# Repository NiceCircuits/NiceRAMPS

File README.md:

ramps_plus
==========
Forked from Ramps 1.4.

Improved version of RAMPS board with ribbon cable connecors and more.

Change log from Ramps 1.4:

- a few ribbon header connectors instead of many pinheaders

- schematic in KiCad

- compatibility with Arduino Due

- separate power supplies for heaters, bed and motors

- 0,5A OC outputs for driwing LED/fans

- SMT power transistors

- blade fuses

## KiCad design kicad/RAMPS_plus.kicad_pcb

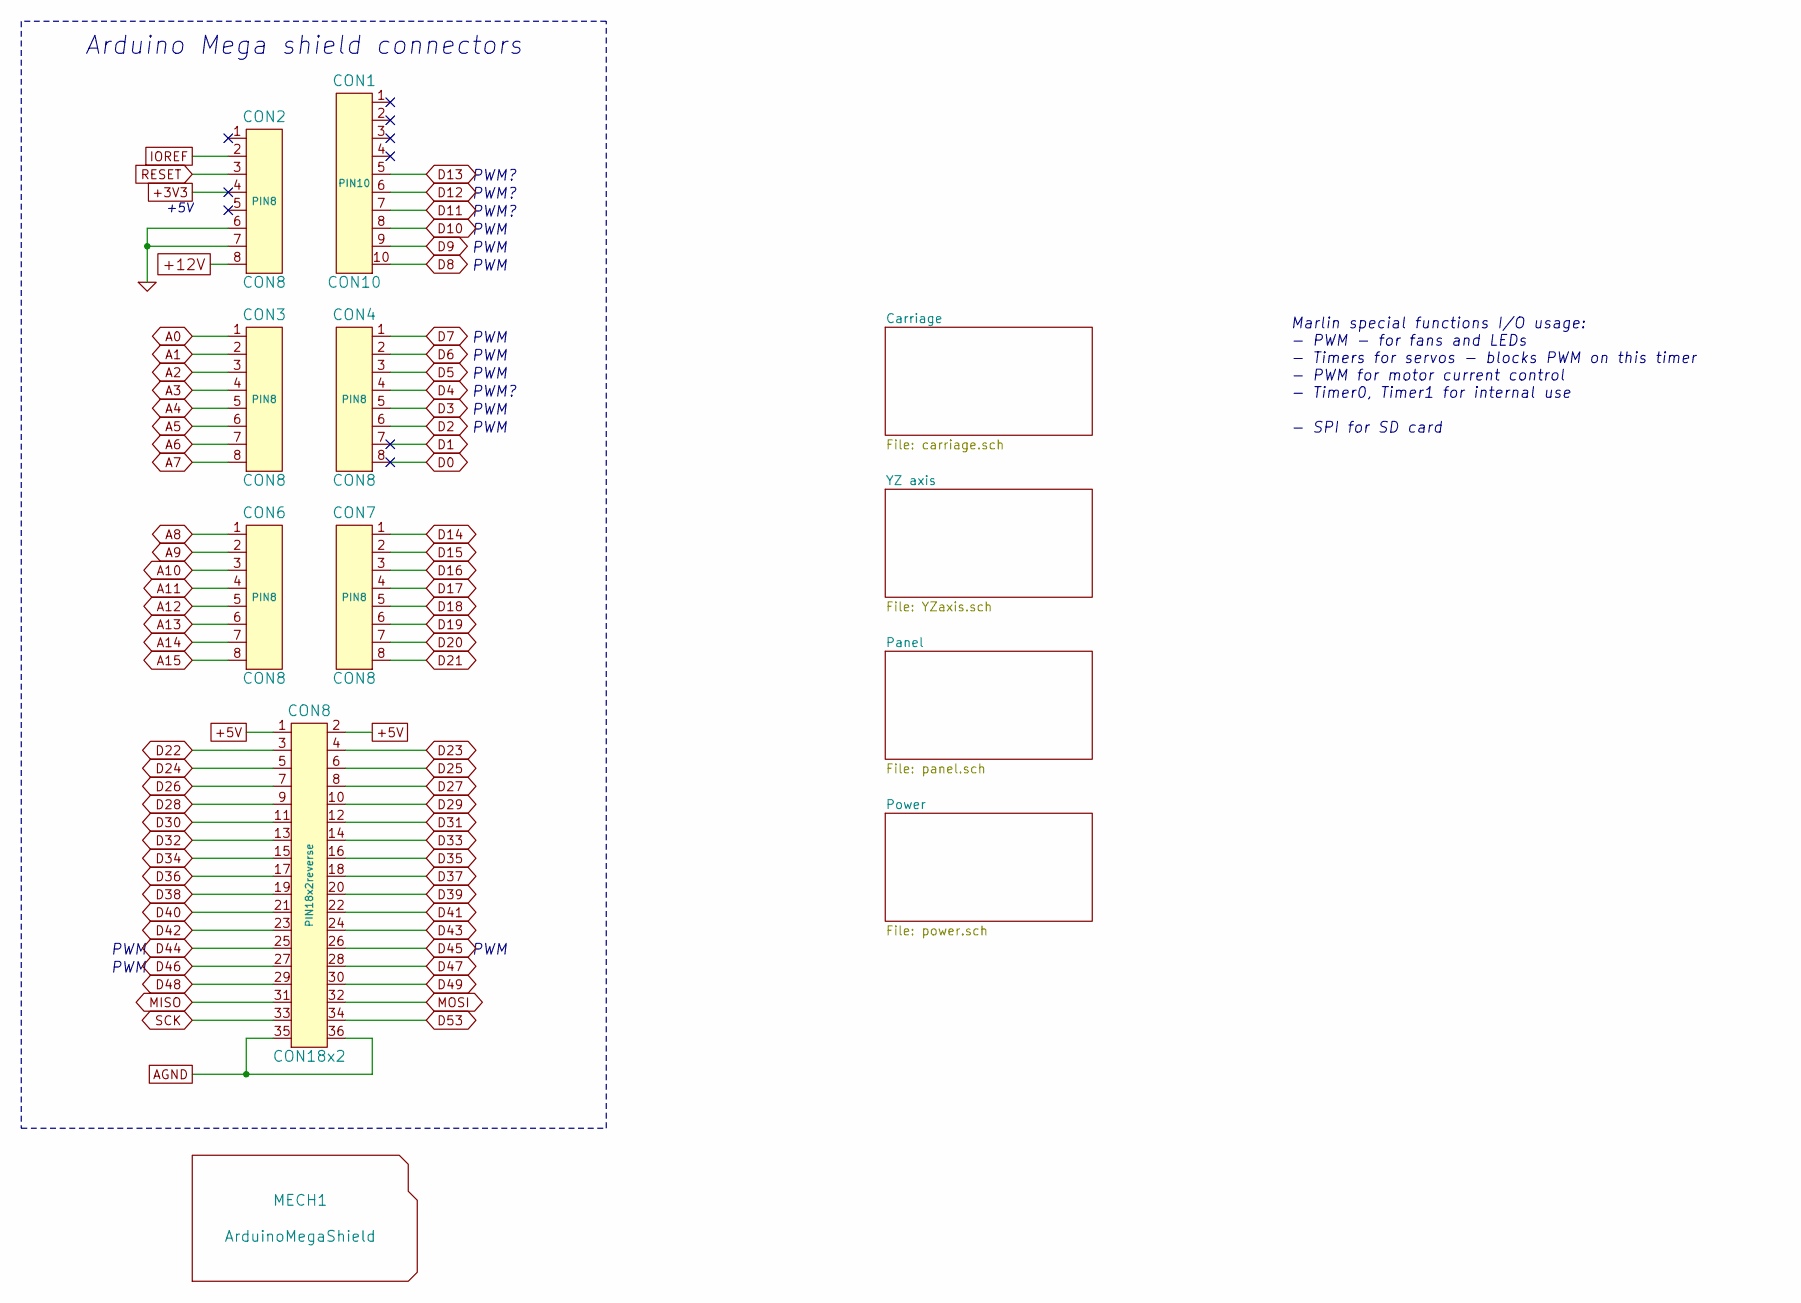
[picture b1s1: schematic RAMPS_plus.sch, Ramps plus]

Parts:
CON1: CON10; PIN10
CON2, CON3, CON4, CON6, CON7: CON8; PIN8
CON8: CON18x2; PIN18x2reverse
MECH1: ArduinoMegaShield

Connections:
+5V: CON8.1, CON8.2; also elsewhere on the board
+12V: CON2.8; also elsewhere on the board
A0: CON3.1; also elsewhere on the board
A1: CON3.2; also elsewhere on the board
A2: CON3.3; also elsewhere on the board
A4: CON3.5; also elsewhere on the board
A5: CON3.6; also elsewhere on the board
A6: CON3.7; also elsewhere on the board
A7: CON3.8; also elsewhere on the board
A8: CON6.1; also elsewhere on the board
A9: CON6.2; also elsewhere on the board
A10: CON6.3; also elsewhere on the board
A11: CON6.4; also elsewhere on the board
A12: CON6.5; also elsewhere on the board
A13: CON6.6; also elsewhere on the board
A14: CON6.7; also elsewhere on the board
A15: CON6.8; also elsewhere on the board
AGND: CON8.35, CON8.36; also elsewhere on the board
D2: CON4.6; also elsewhere on the board
D3: CON4.5; also elsewhere on the board
D4: CON4.4; also elsewhere on the board
D5: CON4.3; also elsewhere on the board
D6: CON4.2; also elsewhere on the board
D7: CON4.1; also elsewhere on the board
D8: CON1.10; also elsewhere on the board
D9: CON1.9; also elsewhere on the board
D10: CON1.8; also elsewhere on the board
D11: CON1.7; also elsewhere on the board
D12: CON1.6; also elsewhere on the board
D13: CON1.5; also elsewhere on the board
D14: CON7.1; also elsewhere on the board
D15: CON7.2; also elsewhere on the board
D16: CON7.3; also elsewhere on the board
D17: CON7.4; also elsewhere on the board
D20: CON7.7; also elsewhere on the board
D21: CON7.8; also elsewhere on the board
D23: CON8.4; also elsewhere on the board
D24: CON8.5; also elsewhere on the board
D25: CON8.6; also elsewhere on the board
D26: CON8.7; also elsewhere on the board
D27: CON8.8; also elsewhere on the board
D28: CON8.9; also elsewhere on the board
D29: CON8.10; also elsewhere on the board
D30: CON8.11; also elsewhere on the board
D31: CON8.12; also elsewhere on the board
D32: CON8.13; also elsewhere on the board
D33: CON8.14; also elsewhere on the board
D34: CON8.15; also elsewhere on the board
D35: CON8.16; also elsewhere on the board
D36: CON8.17; also elsewhere on the board
D37: CON8.18; also elsewhere on the board
D38: CON8.19; also elsewhere on the board
D39: CON8.20; also elsewhere on the board
D40: CON8.21; also elsewhere on the board
D41: CON8.22; also elsewhere on the board
D42: CON8.23; also elsewhere on the board
D43: CON8.24; also elsewhere on the board
D44: CON8.25; also elsewhere on the board
D45: CON8.26; also elsewhere on the board
D46: CON8.27; also elsewhere on the board
D47: CON8.28; also elsewhere on the board
D49: CON8.30; also elsewhere on the board
D53: CON8.34; also elsewhere on the board
GND: CON2.6, CON2.7; also elsewhere on the board
IOREF: CON2.2; also elsewhere on the board
MISO: CON8.31; also elsewhere on the board
MOSI: CON8.32; also elsewhere on the board
RESET: CON2.3; also elsewhere on the board
SCK: CON8.33; also elsewhere on the board

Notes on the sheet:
Arduino Mega shield connectors
PWM
Marlin special functions I/O usage: - PWM - for fans and LEDs - Timers for servos - blocks PWM on this timer - PWM for motor current control - Timer0, Timer1 for internal use - SPI for SD card
PWM?
+5V

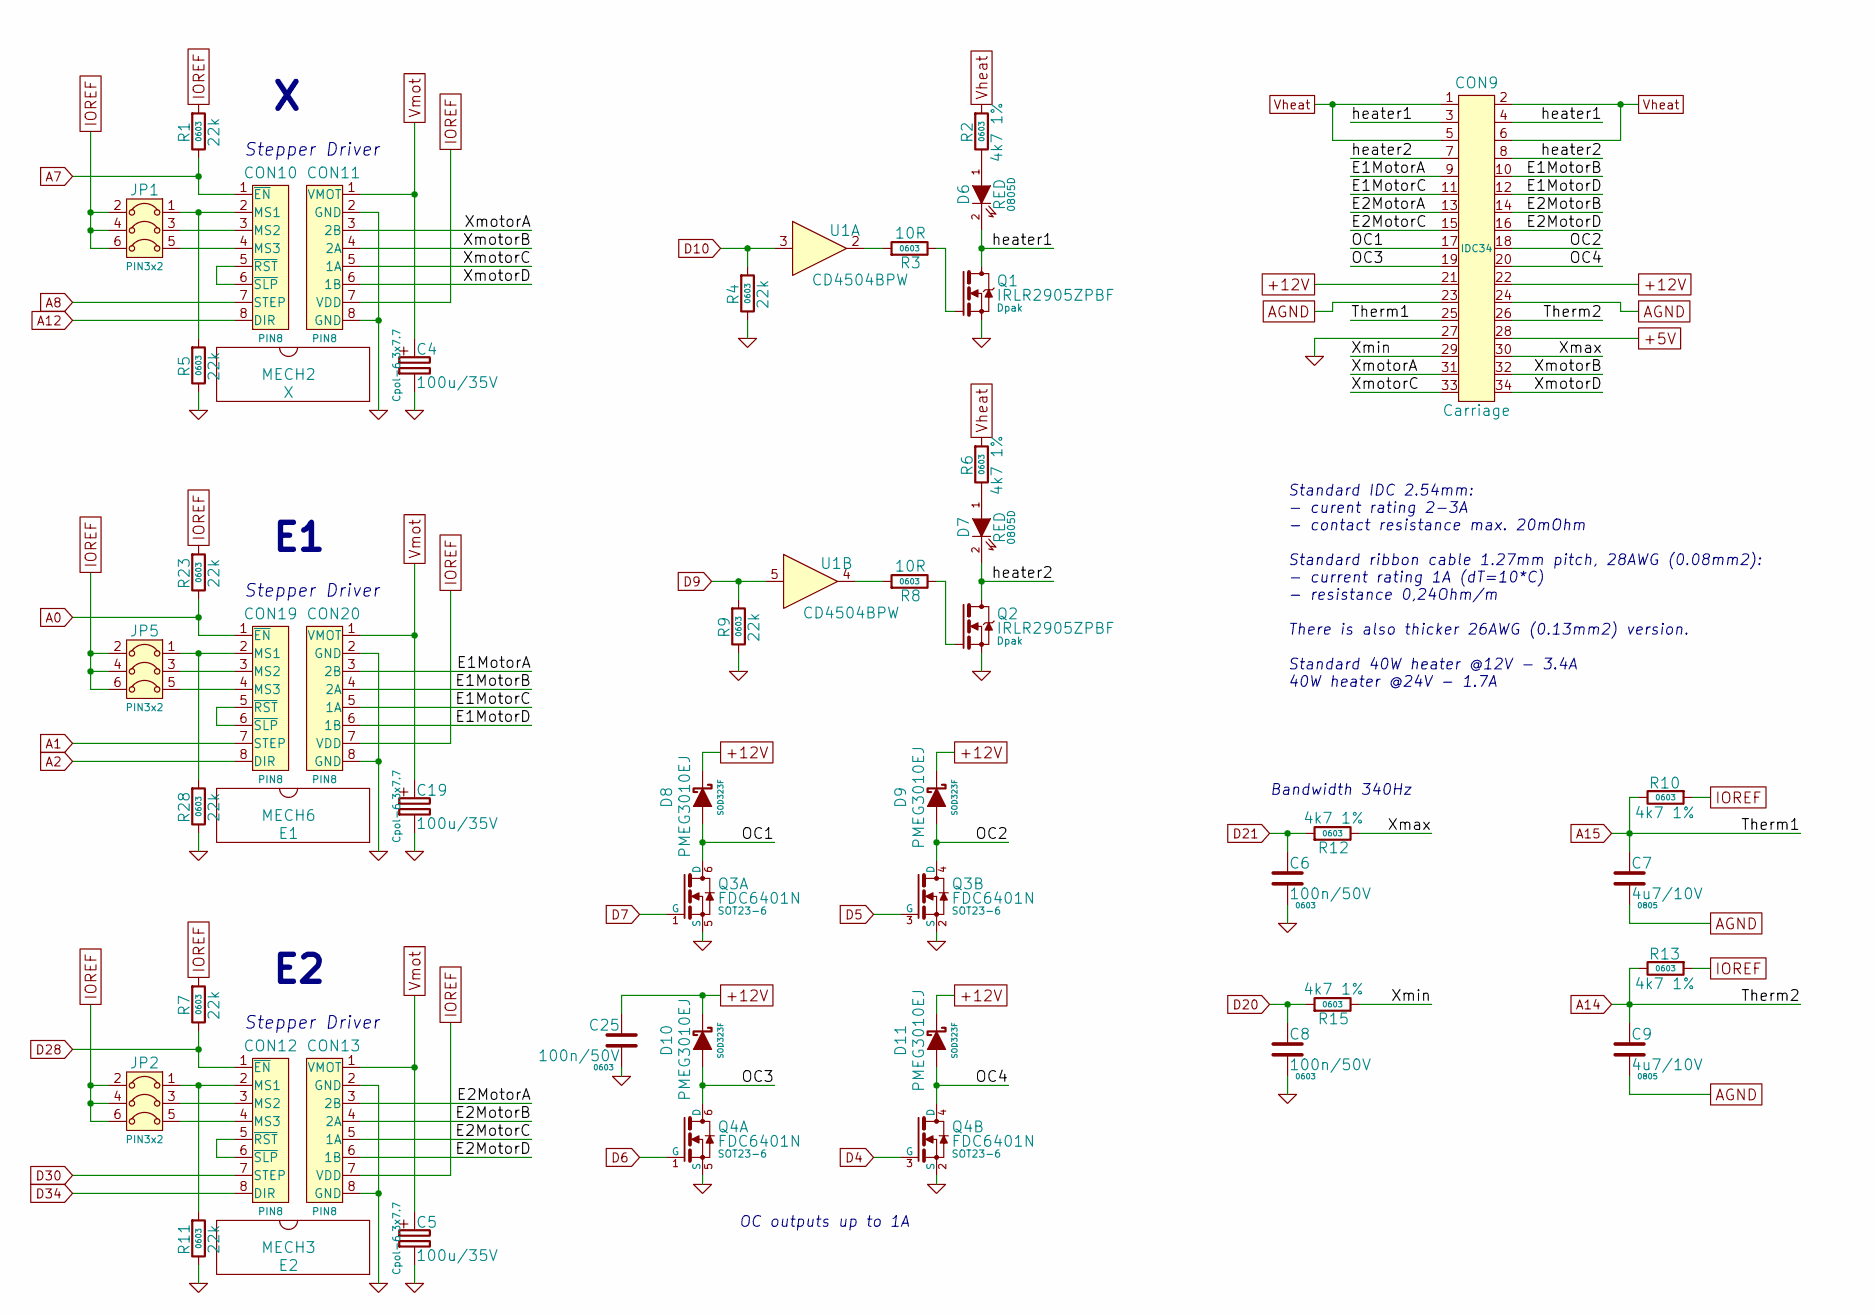
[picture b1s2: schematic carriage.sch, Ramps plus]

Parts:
C4, C5, C19: 100u/35V; Cpol-6.3x7.7
C6, C8, C25: 100n/50V; 0603
C7, C9: 4u7/10V; 0805
CON9: Carriage; IDC34
CON10, CON12, CON19: Stepstick_Left_Connector; PIN8
CON11, CON13, CON20: Stepstick_Right_Connector; PIN8
D6, D7: RED; 0805D
D8, D9, D10, D11: PMEG3010EJ; SOD323F
JP1, JP2, JP5: Jumper3; PIN3x2
MECH2: X
MECH3: E2
MECH6: E1
Q1, Q2: IRLR2905ZPBF; Dpak
Q3, Q4: FDC6401N; SOT23-6
R1, R4, R5, R7, R9, R11, R23, R28: 22k; 0603
R2, R6, R10, R12, R13, R15: 4k7 1%; 0603
R3, R8: 10R; 0603
U1: CD4504BPW; TSSOP16

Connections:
+5V: CON9.28; also elsewhere on the board
+12V: C25.1, CON9.21, CON9.22, D8.1, D9.1, D10.1, D11.1; also elsewhere on the board
/Carriage/E1MotorA: CON9.9, CON20.3 (2B)
/Carriage/E1MotorB: CON9.10, CON20.4 (2A)
/Carriage/E1MotorC: CON9.11, CON20.5 (1A)
/Carriage/E1MotorD: CON9.12, CON20.6 (1B)
/Carriage/E2MotorA: CON9.13, CON13.3 (2B)
/Carriage/E2MotorB: CON9.14, CON13.4 (2A)
/Carriage/E2MotorC: CON9.15, CON13.5 (1A)
/Carriage/E2MotorD: CON9.16, CON13.6 (1B)
/Carriage/OC1: CON9.17, D8.2, Q3.6 (D)
/Carriage/OC2: CON9.18, D9.2, Q3.4 (D)
/Carriage/OC3: CON9.19, D10.2, Q4.6 (D)
/Carriage/OC4: CON9.20, D11.2, Q4.4 (D)
/Carriage/Xmax: CON9.30, R12.2
/Carriage/Xmin: CON9.29, R15.2
/Carriage/XmotorA: CON9.31, CON11.3 (2B)
/Carriage/XmotorB: CON9.32, CON11.4 (2A)
/Carriage/XmotorC: CON9.33, CON11.5 (1A)
/Carriage/XmotorD: CON9.34, CON11.6 (1B)
/Carriage/heater1: CON9.3, CON9.4, D6.2 (K), Q1.4 (D)
/Carriage/heater2: CON9.7, CON9.8, D7.2 (K), Q2.4 (D)
A0: CON19.1 (~EN), R23.2; also elsewhere on the board
A1: CON19.7 (STEP); also elsewhere on the board
A2: CON19.8 (DIR); also elsewhere on the board
A7: CON10.1 (~EN), R1.2; also elsewhere on the board
A8: CON10.7 (STEP); also elsewhere on the board
A12: CON10.8 (DIR); also elsewhere on the board
A14: C9.1, CON9.26, R13.2; also elsewhere on the board
A15: C7.1, CON9.25, R10.2; also elsewhere on the board
AGND: C7.2, C9.2, CON9.23, CON9.24; also elsewhere on the board
D4: Q4.3 (G); also elsewhere on the board
D5: Q3.3 (G); also elsewhere on the board
D6: Q4.1 (G); also elsewhere on the board
D7: Q3.1 (G); also elsewhere on the board
D9: R9.1, U1.5 (IN2); also elsewhere on the board
D10: R4.1, U1.3 (IN1); also elsewhere on the board
D20: C8.1, R15.1; also elsewhere on the board
D21: C6.1, R12.1; also elsewhere on the board
D28: CON12.1 (~EN), R7.2; also elsewhere on the board
D30: CON12.7 (STEP); also elsewhere on the board
D34: CON12.8 (DIR); also elsewhere on the board
GND: C4.2, C5.2, C6.2, C8.2, C19.2, C25.2, CON9.27, CON11.2 (GND), CON11.8 (GND), CON13.2 (GND), CON13.8 (GND), CON20.2 (GND), CON20.8 (GND), Q1.3 (S), Q2.3 (S), Q3.2 (S), Q3.5 (S), Q4.2 (S), Q4.5 (S), R4.2, R5.2, R9.2, R11.2, R28.2; also elsewhere on the board
IOREF: CON11.7 (VDD), CON13.7 (VDD), CON20.7 (VDD), JP1.2, JP1.4, JP1.6, JP2.2, JP2.4, JP2.6, JP5.2, JP5.4, JP5.6, R1.1, R7.1, R10.1, R13.1, R23.1; also elsewhere on the board
unnamed: CON10.2 (MS1), JP1.1, R5.1
unnamed: CON10.3 (MS2), JP1.3
unnamed: CON10.4 (MS3), JP1.5
unnamed: CON10.5 (~RST), CON10.6 (~SLP)
unnamed: CON12.2 (MS1), JP2.1, R11.1
unnamed: CON12.3 (MS2), JP2.3
unnamed: CON12.4 (MS3), JP2.5
unnamed: CON12.5 (~RST), CON12.6 (~SLP)
unnamed: CON19.2 (MS1), JP5.1, R28.1
unnamed: CON19.3 (MS2), JP5.3
unnamed: CON19.4 (MS3), JP5.5
unnamed: CON19.5 (~RST), CON19.6 (~SLP)
unnamed: D6.1 (A), R2.2
unnamed: D7.1 (A), R6.2
unnamed: Q1.1 (G), R3.2
unnamed: Q2.1 (G), R8.2
unnamed: R3.1, U1.2 (OUT1)
unnamed: R8.1, U1.4 (OUT2)
Vheat: CON9.1, CON9.2, CON9.5, CON9.6, R2.1, R6.1; also elsewhere on the board
Vmot: C4.1, C5.1, C19.1, CON11.1 (VMOT), CON13.1 (VMOT), CON20.1 (VMOT); also elsewhere on the board

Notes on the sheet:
Standard IDC 2.54mm: - curent rating 2-3A - contact resistance max. 20mOhm Standard ribbon cable 1.27mm pitch, 28AWG (0.08mm2): - current rating 1A (dT=10*C) - resistance 0,24Ohm/m There is also thicker 26AWG (0.13mm2) version. Standard 40W heater @12V - 3.4A 40W heater @24V - 1.7A
Bandwidth 340Hz
OC outputs up to 1A
Stepper Driver

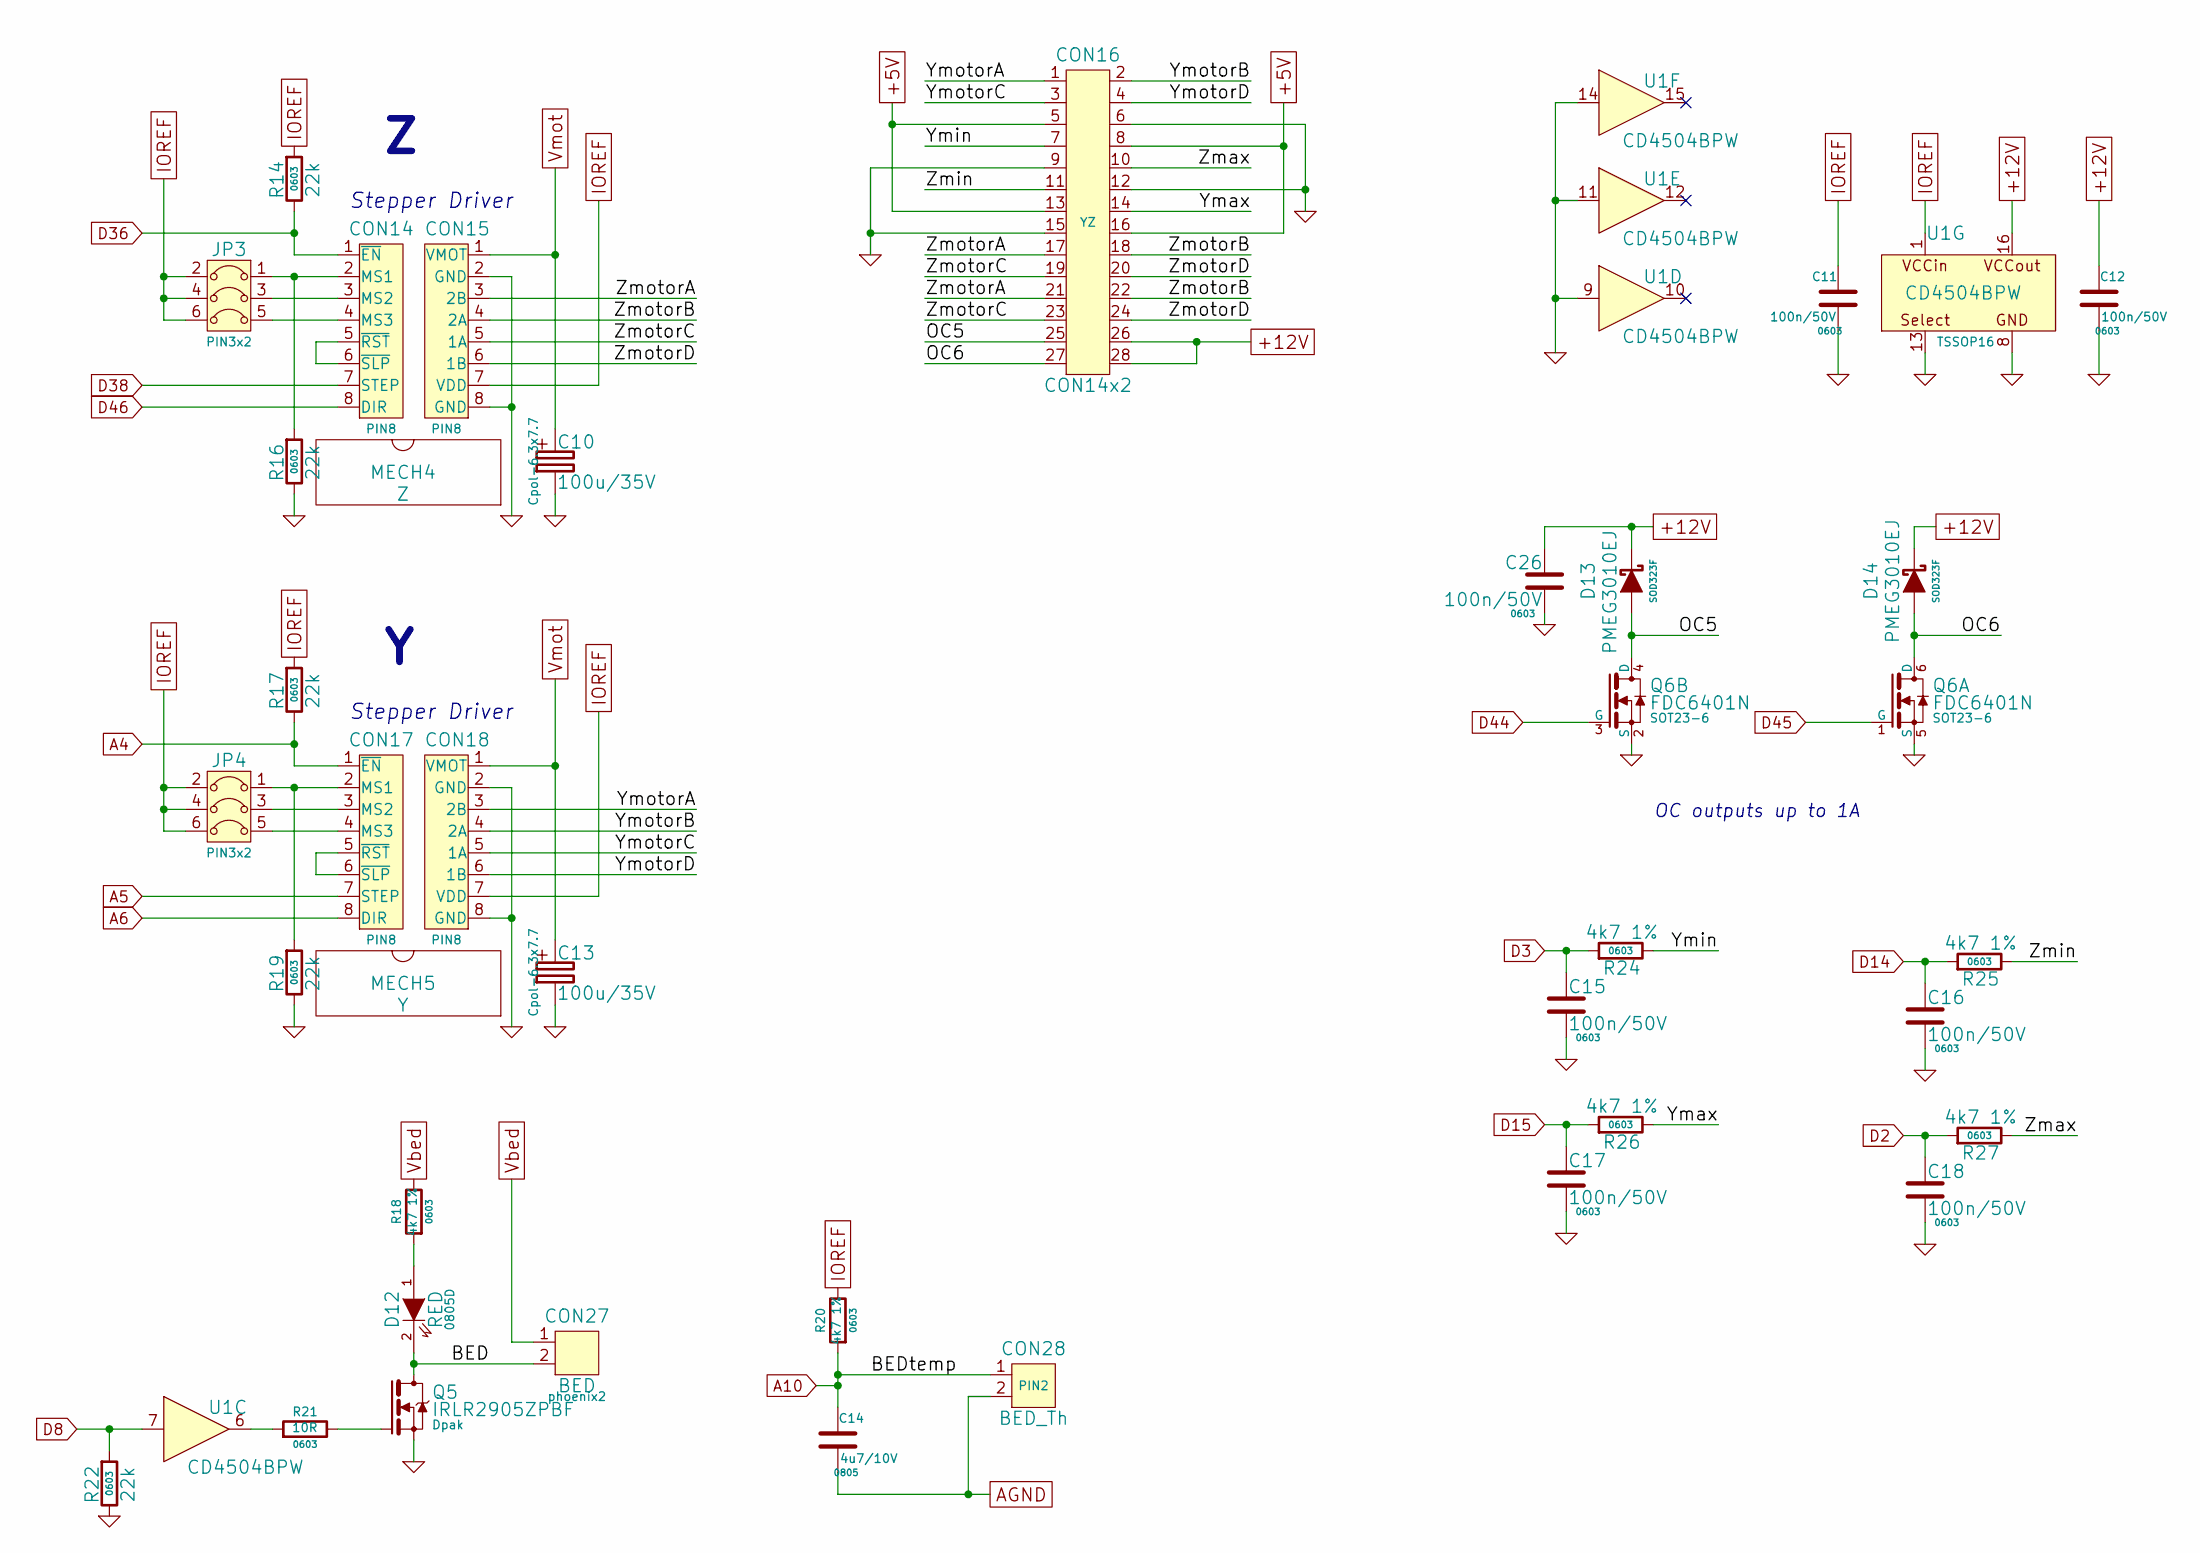
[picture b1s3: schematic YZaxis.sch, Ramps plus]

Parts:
C10, C13: 100u/35V; Cpol-6.3x7.7
C11, C12, C15, C16, C17, C18, C26: 100n/50V; 0603
C14: 4u7/10V; 0805
CON14, CON17: Stepstick_Left_Connector; PIN8
CON15, CON18: Stepstick_Right_Connector; PIN8
CON16: CON14x2; YZ
CON27: BED; phoenix2
CON28: BED_Th; PIN2
D12: RED; 0805D
D13, D14: PMEG3010EJ; SOD323F
JP3, JP4: Jumper3; PIN3x2
MECH4: Z
MECH5: Y
Q5: IRLR2905ZPBF; Dpak
Q6: FDC6401N; SOT23-6
R14, R16, R17, R19, R22: 22k; 0603
R18, R20, R24, R25, R26, R27: 4k7 1%; 0603
R21: 10R; 0603
U1: CD4504BPW; TSSOP16

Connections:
+5V: CON16.5, CON16.8, CON16.13, CON16.16; also elsewhere on the board
+12V: C12.1, C26.1, CON16.26, CON16.28, D13.1, D14.1, U1.16 (VDD); also elsewhere on the board
/YZ axis/BED: CON27.2, D12.2 (K), Q5.4 (D)
/YZ axis/OC5: CON16.25, D13.2, Q6.4 (D)
/YZ axis/OC6: CON16.27, D14.2, Q6.6 (D)
/YZ axis/Ymax: CON16.14, R26.2
/YZ axis/Ymin: CON16.7, R24.2
/YZ axis/YmotorA: CON16.1, CON18.3 (2B)
/YZ axis/YmotorB: CON16.2, CON18.4 (2A)
/YZ axis/YmotorC: CON16.3, CON18.5 (1A)
/YZ axis/YmotorD: CON16.4, CON18.6 (1B)
/YZ axis/Zmax: CON16.10, R27.2
/YZ axis/Zmin: CON16.11, R25.2
/YZ axis/ZmotorA: CON15.3 (2B), CON16.17, CON16.21
/YZ axis/ZmotorB: CON15.4 (2A), CON16.18, CON16.22
/YZ axis/ZmotorC: CON15.5 (1A), CON16.19, CON16.23
/YZ axis/ZmotorD: CON15.6 (1B), CON16.20, CON16.24
A4: CON17.1 (~EN), R17.2; also elsewhere on the board
A5: CON17.7 (STEP); also elsewhere on the board
A6: CON17.8 (DIR); also elsewhere on the board
A10: C14.1, CON28.1, R20.1; also elsewhere on the board
AGND: C14.2, CON28.2; also elsewhere on the board
D2: C18.1, R27.1; also elsewhere on the board
D3: C15.1, R24.1; also elsewhere on the board
D8: R22.1, U1.7 (IN3); also elsewhere on the board
D14: C16.1, R25.1; also elsewhere on the board
D15: C17.1, R26.1; also elsewhere on the board
D36: CON14.1 (~EN), R14.2; also elsewhere on the board
D38: CON14.7 (STEP); also elsewhere on the board
D44: Q6.3 (G); also elsewhere on the board
D45: Q6.1 (G); also elsewhere on the board
D46: CON14.8 (DIR); also elsewhere on the board
GND: C10.2, C11.2, C12.2, C13.2, C15.2, C16.2, C17.2, C18.2, C26.2, CON15.2 (GND), CON15.8 (GND), CON16.6, CON16.9, CON16.12, CON16.15, CON18.2 (GND), CON18.8 (GND), Q5.3 (S), Q6.2 (S), Q6.5 (S), R16.2, R19.2, R22.2, U1.8 (GND), U1.9 (IN4), U1.11 (IN5), U1.13 (GND), U1.14 (IN6); also elsewhere on the board
IOREF: C11.1, CON15.7 (VDD), CON18.7 (VDD), JP3.2, JP3.4, JP3.6, JP4.2, JP4.4, JP4.6, R14.1, R17.1, R20.2, U1.1 (VCC); also elsewhere on the board
unnamed: CON14.2 (MS1), JP3.1, R16.1
unnamed: CON14.3 (MS2), JP3.3
unnamed: CON14.4 (MS3), JP3.5
unnamed: CON14.5 (~RST), CON14.6 (~SLP)
unnamed: CON17.2 (MS1), JP4.1, R19.1
unnamed: CON17.3 (MS2), JP4.3
unnamed: CON17.4 (MS3), JP4.5
unnamed: CON17.5 (~RST), CON17.6 (~SLP)
unnamed: D12.1 (A), R18.1
unnamed: Q5.1 (G), R21.2
unnamed: R21.1, U1.6 (OUT3)
Vbed: CON27.1, R18.2; also elsewhere on the board
Vmot: C10.1, C13.1, CON15.1 (VMOT), CON18.1 (VMOT); also elsewhere on the board

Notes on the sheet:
OC outputs up to 1A
Stepper Driver

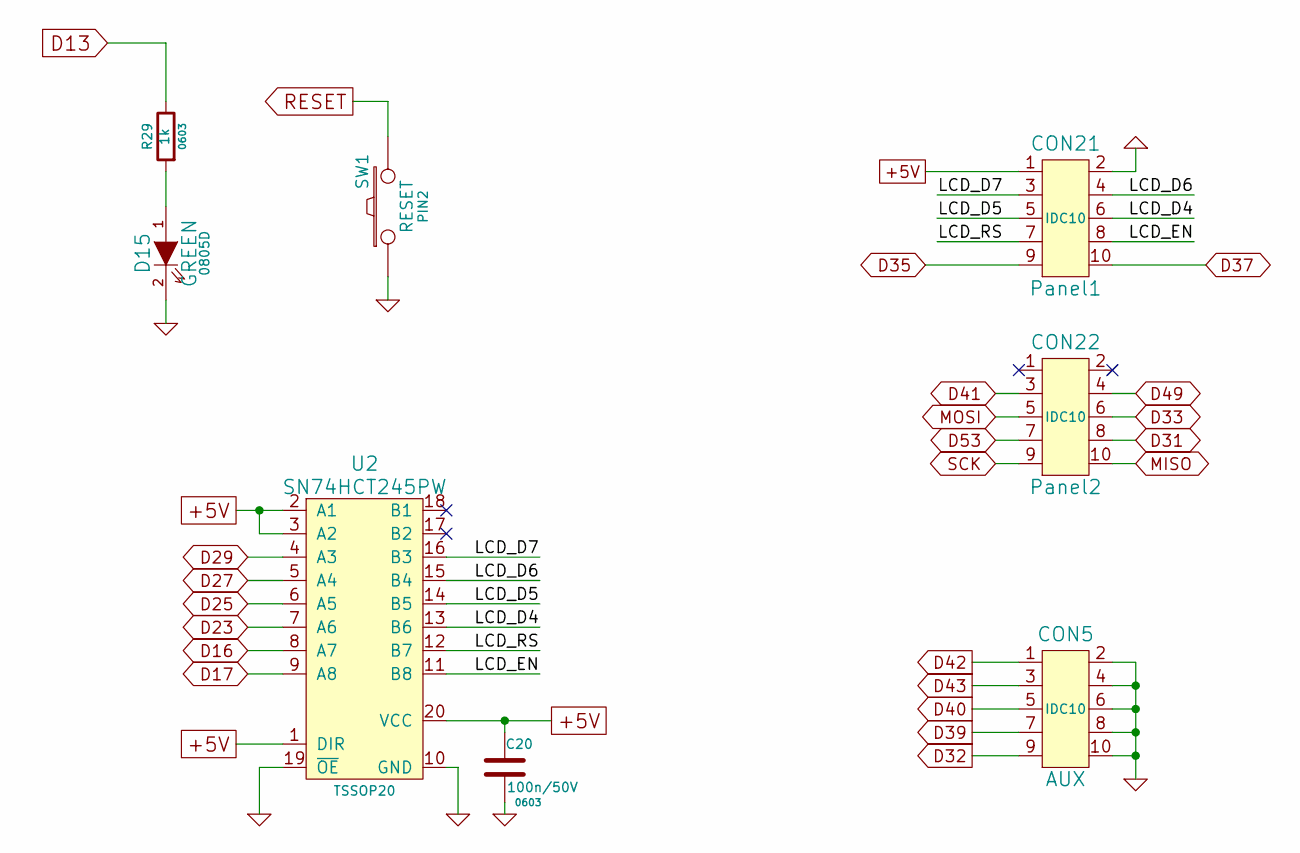
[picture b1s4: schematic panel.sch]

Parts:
C20: 100n/50V; 0603
CON5: AUX; IDC10
CON21: Panel1; IDC10
CON22: Panel2; IDC10
D15: GREEN; 0805D
R29: 1k; 0603
SW1: RESET; PIN2
U2: SN74HCT245PW; TSSOP20

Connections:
+5V: C20.1, CON21.1, U2.1 (DIR), U2.2 (A1), U2.3 (A2), U2.20 (VCC); also elsewhere on the board
/Panel/LCD_D4: CON21.6, U2.13 (B6)
/Panel/LCD_D5: CON21.5, U2.14 (B5)
/Panel/LCD_D6: CON21.4, U2.15 (B4)
/Panel/LCD_D7: CON21.3, U2.16 (B3)
/Panel/LCD_EN: CON21.8, U2.11 (B8)
/Panel/LCD_RS: CON21.7, U2.12 (B7)
D13: R29.2; also elsewhere on the board
D16: U2.8 (A7); also elsewhere on the board
D17: U2.9 (A8); also elsewhere on the board
D23: U2.7 (A6); also elsewhere on the board
D25: U2.6 (A5); also elsewhere on the board
D27: U2.5 (A4); also elsewhere on the board
D29: U2.4 (A3); also elsewhere on the board
D31: CON22.8; also elsewhere on the board
D32: CON5.9; also elsewhere on the board
D33: CON22.6; also elsewhere on the board
D35: CON21.9; also elsewhere on the board
D37: CON21.10; also elsewhere on the board
D39: CON5.7; also elsewhere on the board
D40: CON5.5; also elsewhere on the board
D41: CON22.3; also elsewhere on the board
D42: CON5.1; also elsewhere on the board
D43: CON5.3; also elsewhere on the board
D49: CON22.4; also elsewhere on the board
D53: CON22.7; also elsewhere on the board
GND: C20.2, CON5.2, CON5.4, CON5.6, CON5.8, CON5.10, CON21.2, D15.2 (K), SW1.1, U2.10 (GND), U2.19 (~OE); also elsewhere on the board
MISO: CON22.10; also elsewhere on the board
MOSI: CON22.5; also elsewhere on the board
unnamed: D15.1 (A), R29.1
RESET: SW1.2; also elsewhere on the board
SCK: CON22.9; also elsewhere on the board

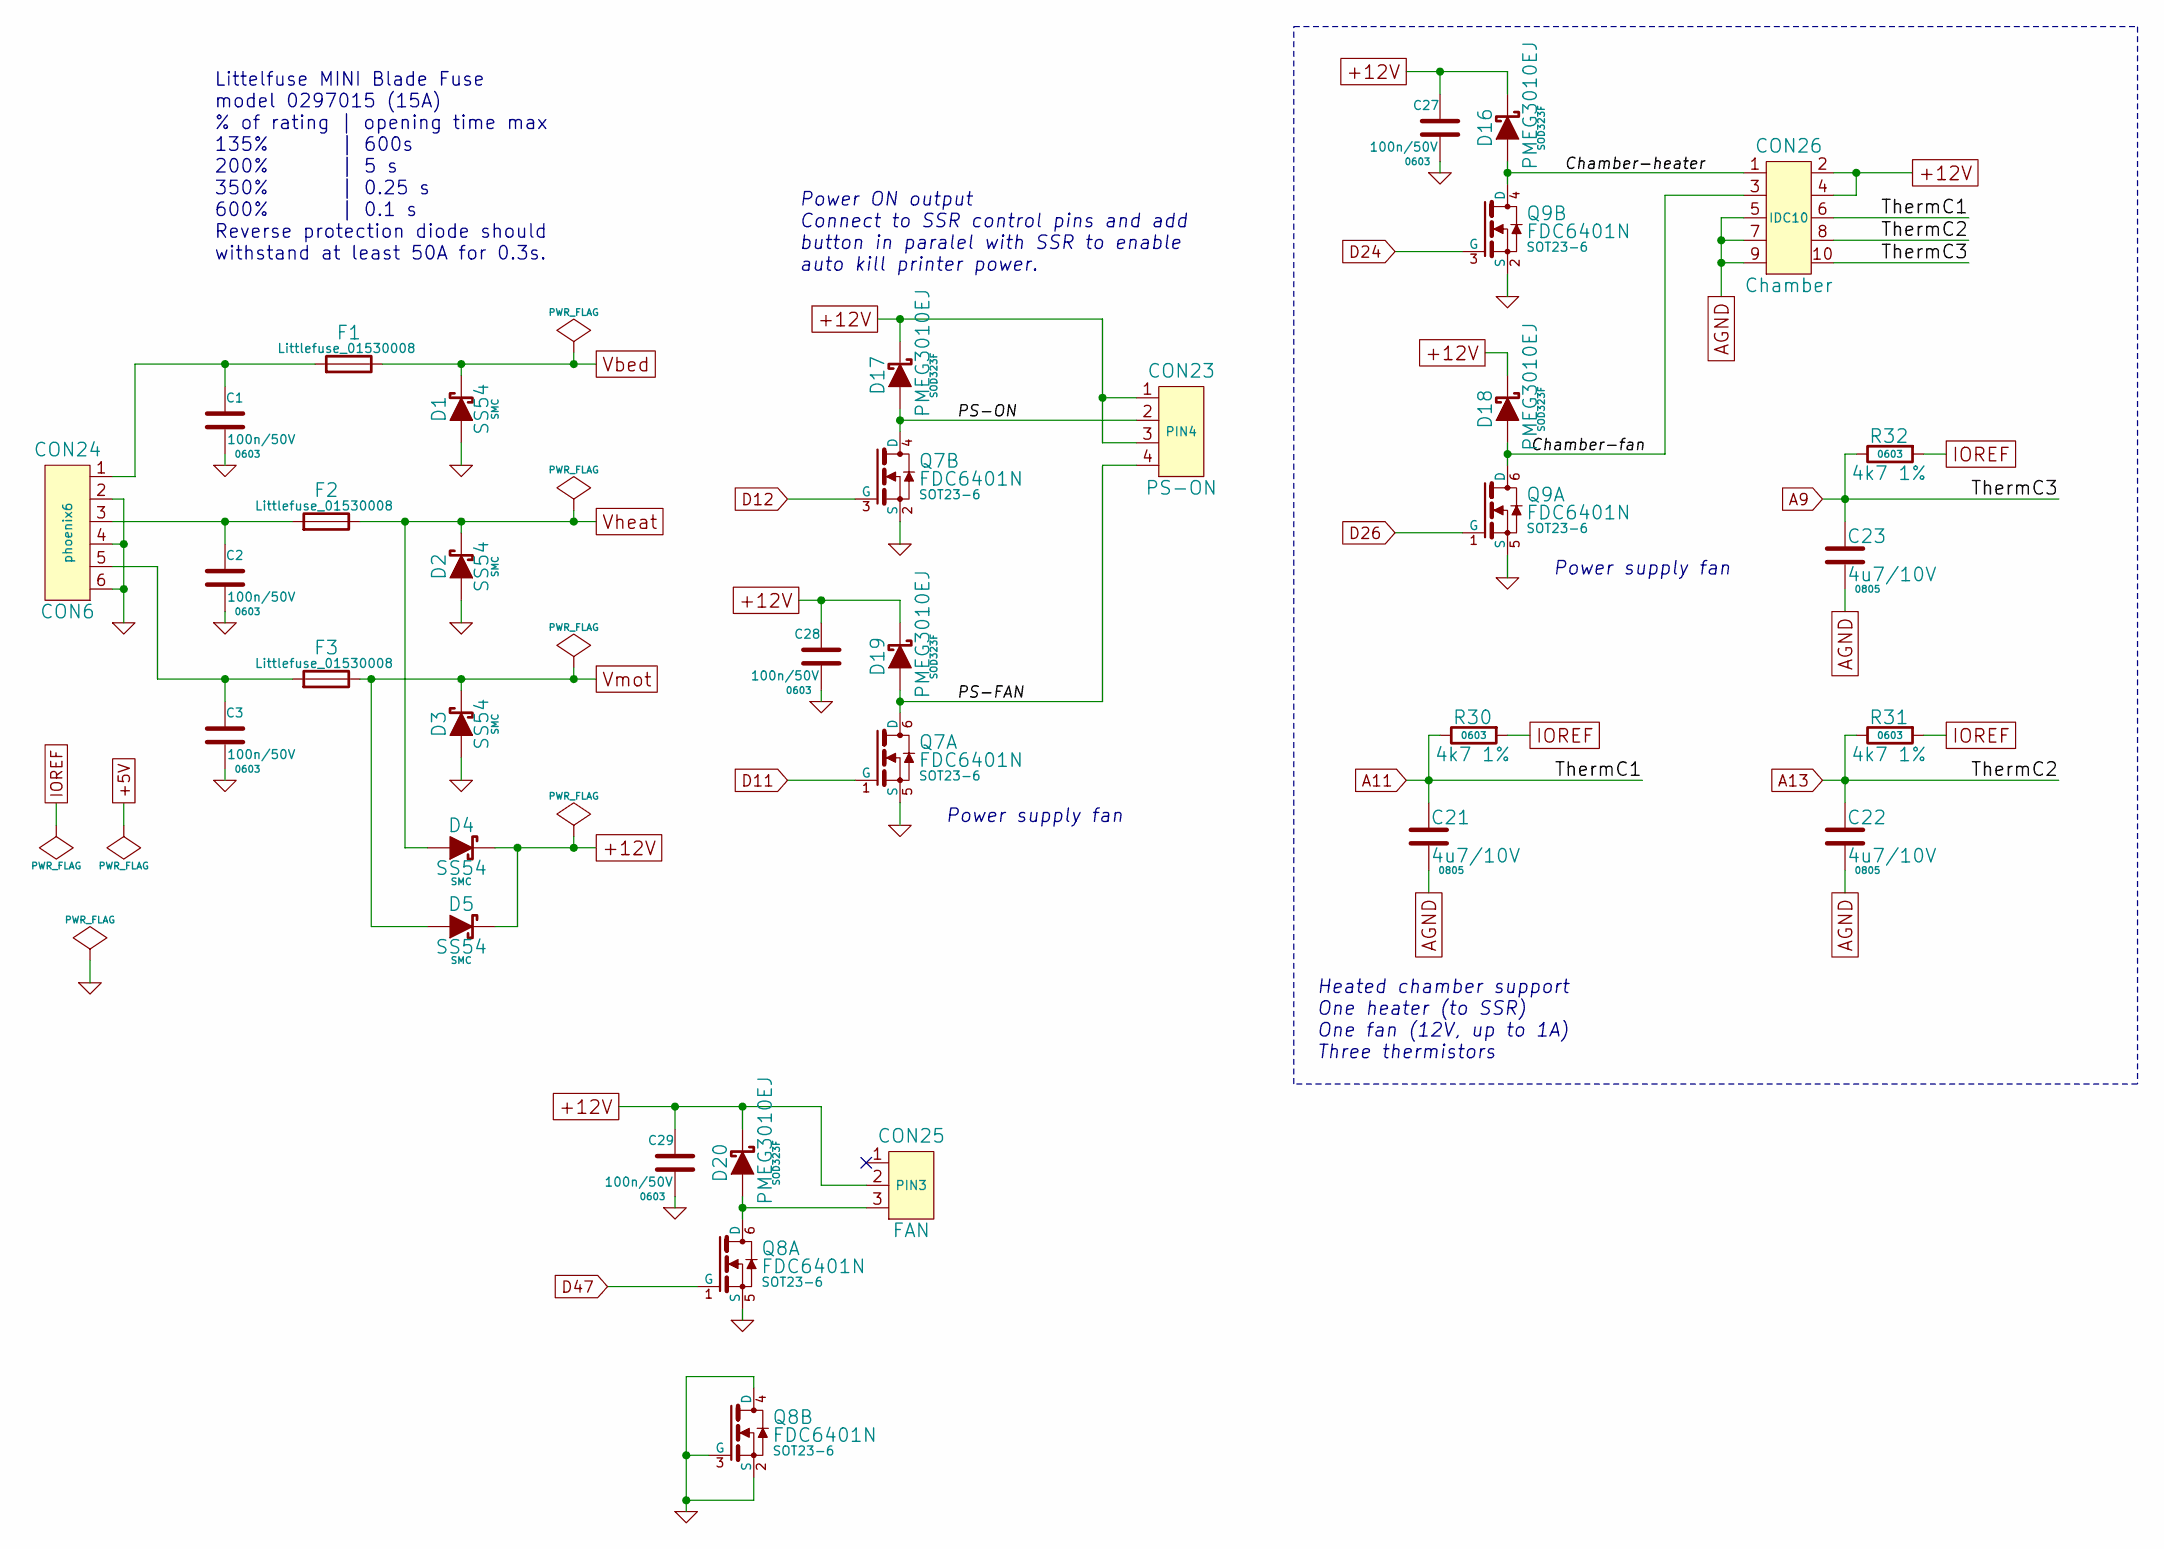
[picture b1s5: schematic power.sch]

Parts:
C1, C2, C3, C27, C28, C29: 100n/50V; 0603
C21, C22, C23: 4u7/10V; 0805
CON23: PS-ON; PIN4
CON24: CON6; phoenix6
CON25: FAN; PIN3
CON26: Chamber; IDC10
D1, D2, D3, D4, D5: SS54; SMC
D16, D17, D18, D19, D20: PMEG3010EJ; SOD323F
F1, F2, F3: MINI_Blade_Fuse_Holder; Littlefuse_01530008
Q7, Q8, Q9: FDC6401N; SOT23-6
R30, R31, R32: 4k7 1%; 0603

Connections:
+12V: C27.1, C28.1, C29.1, CON23.1, CON23.3, CON25.2, CON26.2, CON26.4, D4.1, D5.1, D16.1, D17.1, D18.1, D19.1, D20.1; also elsewhere on the board
/Power/Chamber-fan: CON26.3, D18.2, Q9.6 (D)
/Power/Chamber-heater: CON26.1, D16.2, Q9.4 (D)
/Power/PS-FAN: CON23.4, D19.2, Q7.6 (D)
/Power/PS-ON: CON23.2, D17.2, Q7.4 (D)
A9: C23.1, CON26.10, R32.2; also elsewhere on the board
A11: C21.1, CON26.6, R30.2; also elsewhere on the board
A13: C22.1, CON26.8, R31.2; also elsewhere on the board
AGND: C21.2, C22.2, C23.2, CON26.5, CON26.7, CON26.9; also elsewhere on the board
D11: Q7.1 (G); also elsewhere on the board
D12: Q7.3 (G); also elsewhere on the board
D24: Q9.3 (G); also elsewhere on the board
D26: Q9.1 (G); also elsewhere on the board
D47: Q8.1 (G); also elsewhere on the board
GND: C1.2, C2.2, C3.2, C27.2, C28.2, C29.2, CON24.2, CON24.4, CON24.6, D1.2, D2.2, D3.2, Q7.2 (S), Q7.5 (S), Q8.2 (S), Q8.3 (G), Q8.4 (D), Q8.5 (S), Q9.2 (S), Q9.5 (S); also elsewhere on the board
IOREF: R30.1, R31.1, R32.1; also elsewhere on the board
unnamed: C1.1, CON24.1, F1.1
unnamed: C2.1, CON24.3, F2.1
unnamed: C3.1, CON24.5, F3.1
unnamed: CON25.3, D20.2, Q8.6 (D)
Vbed: D1.1, F1.2; also elsewhere on the board
Vheat: D2.1, D4.2, F2.2; also elsewhere on the board
Vmot: D3.1, D5.2, F3.2; also elsewhere on the board

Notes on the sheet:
Littelfuse MINI Blade Fuse model 0297015 (15A) % of rating | opening time max 135% | 600s 200% | 5 s 350% | 0.25 s 600% | 0.1 s Reverse protection diode should withstand at least 50A for 0.3s.
Power ON output Connect to SSR control pins and add button in paralel with SSR to enable auto kill printer power.
Power supply fan
Heated chamber support One heater (to SSR) One fan (12V, up to 1A) Three thermistors
